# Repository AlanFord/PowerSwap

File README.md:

# PowerSwap
PowerSwap board for the Contextual Electronics course

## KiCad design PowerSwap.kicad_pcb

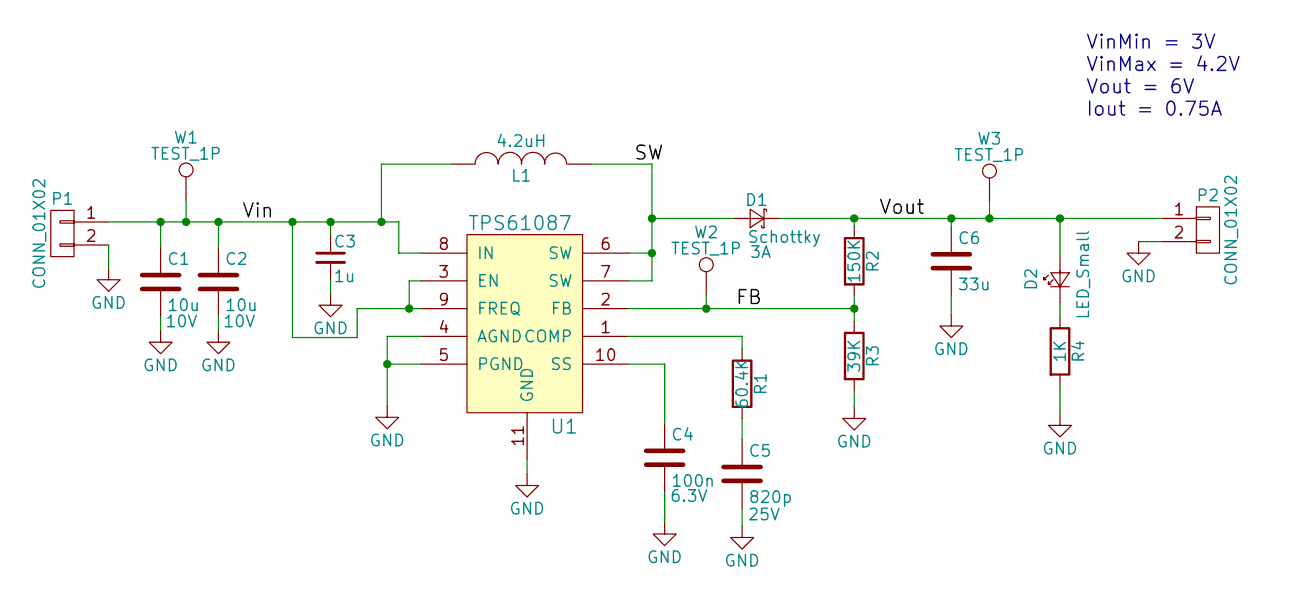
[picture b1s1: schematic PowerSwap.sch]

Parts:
C1, C2: 10u; C_1206_HandSoldering; Voltage 10V
C3: 1u; C_0805_HandSoldering
C4: 100n; C_0805_HandSoldering; Voltage 6.3V
C5: 820p; C_0805_HandSoldering; Voltage 25V
C6: 33u; C_1206_HandSoldering
D1: Schottky; SMA_Handsoldering; MPN SK310A-TP
D2: LED_Small; LED_0805
L1: 4.2uH; SRR5028; MPN SRR5028-4R2Y
P1, P2: CONN_01X02; Pin_Header_Straight_1x02
R1: 60.4K; R_0805_HandSoldering
R2: 150K; R_0805_HandSoldering
R3: 39K; R_0805_HandSoldering
R4: 1K; R_0805_HandSoldering
U1: TPS61087; MPN TPS61087DRCR
W1, W2, W3: TEST_1P; Measurement_Point_Round-SMD-Pad_Small

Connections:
/FB: R2.2, R3.1, U1.2 (FB), W2.1
/SW: D1.2 (A), L1.1, U1.6 (SW), U1.7 (SW)
/Vin: C1.1, C2.1, C3.1, L1.2, P1.1, U1.3 (EN), U1.8 (IN), U1.9 (FREQ), W1.1
/Vout: C6.1, D1.1 (K), D2.2 (A), P2.1, R2.1, W3.1
GND: C1.2, C2.2, C3.2, C4.2, C5.2, C6.2, P1.2, P2.2, R3.2, R4.2, U1.4 (AGND), U1.5 (PGND), U1.11 (GND)
unnamed: C4.1, U1.10 (SS)
unnamed: C5.1, R1.2
unnamed: D2.1 (K), R4.1
unnamed: R1.1, U1.1 (COMP)

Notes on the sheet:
VinMin = 3V VinMax = 4.2V Vout = 6V Iout = 0.75A

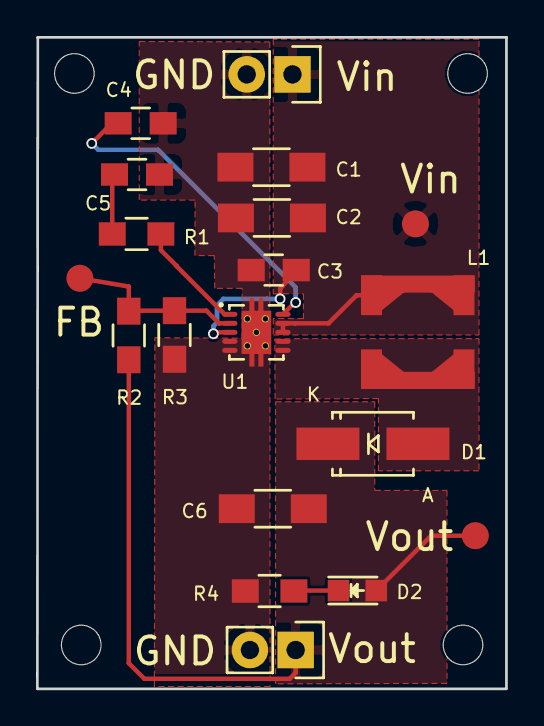
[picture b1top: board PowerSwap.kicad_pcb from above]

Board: 2 copper layers, 26.1 x 36.2 mm, 19 parts (0 on the bottom side), 9 nets.

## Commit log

2017-02-01 initializing kicad
2017-02-18 added footprints and preliminary board layout
2017-02-19 basic track routing complete
2017-02-20 completed layout and generated gerbers
